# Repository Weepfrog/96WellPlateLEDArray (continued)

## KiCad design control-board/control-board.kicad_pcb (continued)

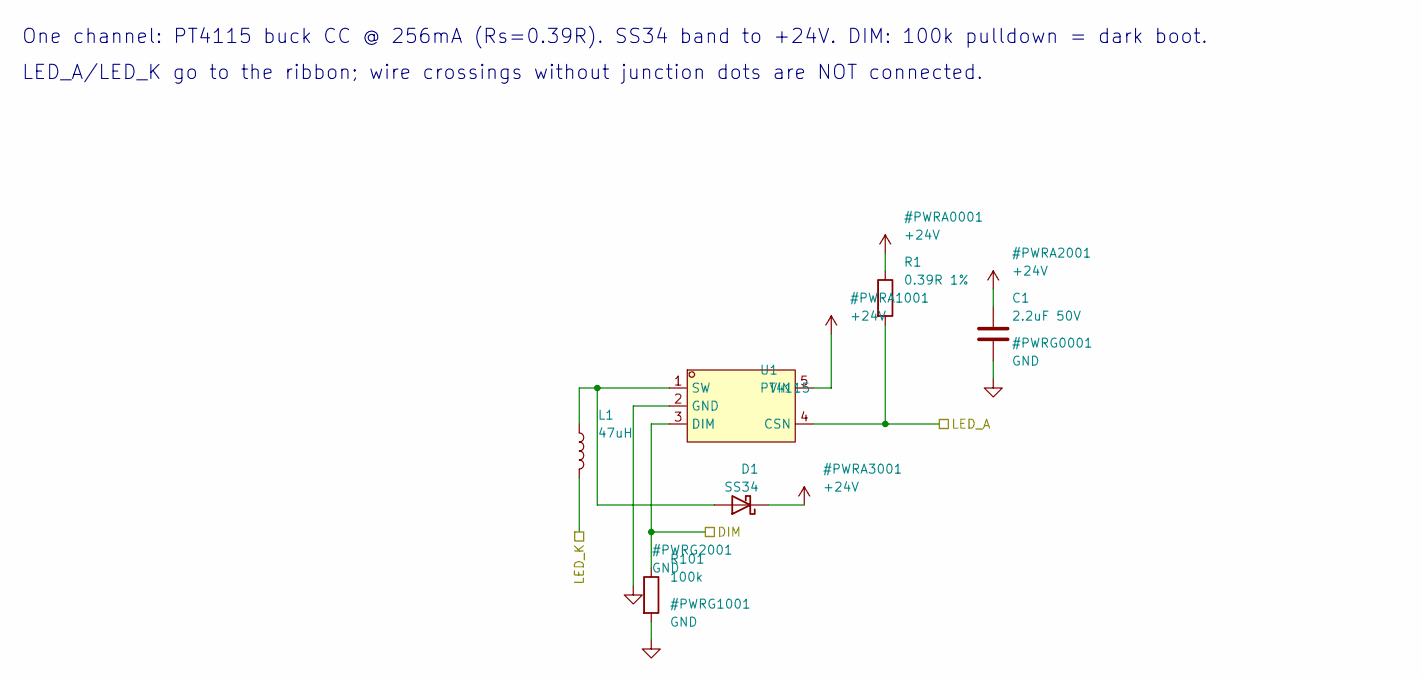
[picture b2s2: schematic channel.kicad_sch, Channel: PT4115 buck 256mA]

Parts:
C1: 2.2uF 50V; C_0805_2012Metric; LCSC C125847
D1: SS34; D_SMA; LCSC C8678
L1: 47uH; L_Sunlord_SWPA4030S; LCSC C54731
R1: 0.39R 1%; R_0805_2012Metric; LCSC C2930218
R101: 100k; R_0603_1608Metric; LCSC C25803
U1: PT4115; SOT-89-5_L4.5-W2.5-P1.50-LS4.5-BR; LCSC C347356

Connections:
+24V: C1.1, D1.1 (K), R1.1, U1.5 (VIN); also elsewhere on the board
/DIM1: R101.1, U1.3 (DIM); also elsewhere on the board
/LED_A33: R1.2, U1.4 (CSN); also elsewhere on the board
/LED_K33: L1.2; also elsewhere on the board
GND: C1.2, R101.2, U1.2 (GND); also elsewhere on the board
unnamed: D1.2 (A), L1.1, U1.1 (SW)

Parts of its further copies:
C2, C3, C4, C5, C6, C7, C8, C9, C10, C11, C12, C13, C14, C15, C16, C17, C18, C19, C20, C21, C22, C23, C24, C25, C26, C27, C28, C29, C30, C31, C32, C33, C34, C35, C36, C37, C38, C39, C40, C41, C42, C43, C44, C45, C46, C47, C48, C49, C50, C51, C52, C53, C54, C55, C56, C57, C58, C59, C60, C61, C62, C63, C64, C65, C66, C67, C68, C69, C70, C71, C72, C73, C74, C75, C76, C77, C78, C79, C80, C81, C82, C83, C84, C85, C86, C87, C88, C89, C90, C91, C92, C93, C94, C95, C96: 2.2uF 50V; C_0805_2012Metric; LCSC C125847
D2, D3, D4, D5, D6, D7, D8, D9, D10, D11, D12, D13, D14, D15, D16, D17, D18, D19, D20, D21, D22, D23, D24, D25, D26, D27, D28, D29, D30, D31, D32, D33, D34, D35, D36, D37, D38, D39, D40, D41, D42, D43, D44, D45, D46, D47, D48, D49, D50, D51, D52, D53, D54, D55, D56, D57, D58, D59, D60, D61, D62, D63, D64, D65, D66, D67, D68, D69, D70, D71, D72, D73, D74, D75, D76, D77, D78, D79, D80, D81, D82, D83, D84, D85, D86, D87, D88, D89, D90, D91, D92, D93, D94, D95, D96: SS34; D_SMA; LCSC C8678
L2, L3, L4, L5, L6, L7, L8, L9, L10, L11, L12, L13, L14, L15, L16, L17, L18, L19, L20, L21, L22, L23, L24, L25, L26, L27, L28, L29, L30, L31, L32, L33, L34, L35, L36, L37, L38, L39, L40, L41, L42, L43, L44, L45, L46, L47, L48, L49, L50, L51, L52, L53, L54, L55, L56, L57, L58, L59, L60, L61, L62, L63, L64, L65, L66, L67, L68, L69, L70, L71, L72, L73, L74, L75, L76, L77, L78, L79, L80, L81, L82, L83, L84, L85, L86, L87, L88, L89, L90, L91, L92, L93, L94, L95, L96: 47uH; L_Sunlord_SWPA4030S; LCSC C54731
R2, R3, R4, R5, R6, R7, R8, R9, R10, R11, R12, R13, R14, R15, R16, R17, R18, R19, R20, R21, R22, R23, R24, R25, R26, R27, R28, R29, R30, R31, R32, R33, R34, R35, R36, R37, R38, R39, R40, R41, R42, R43, R44, R45, R46, R47, R48, R49, R50, R51, R52, R53, R54, R55, R56, R57, R58, R59, R60, R61, R62, R63, R64, R65, R66, R67, R68, R69, R70, R71, R72, R73, R74, R75, R76, R77, R78, R79, R80, R81, R82, R83, R84, R85, R86, R87, R88, R89, R90, R91, R92, R93, R94, R95, R96: 0.39R 1%; R_0805_2012Metric; LCSC C2930218
R102, R103, R104, R105, R106, R107, R108, R109, R110, R111, R112, R113, R114, R115, R116, R117, R118, R119, R120, R121, R122, R123, R124, R125, R126, R127, R128, R129, R130, R131, R132, R133, R134, R135, R136, R137, R138, R139, R140, R141, R142, R143, R144, R145, R146, R147, R148, R149, R150, R151, R152, R153, R154, R155, R156, R157, R158, R159, R160, R161, R162, R163, R164, R165, R166, R167, R168, R169, R170, R171, R172, R173, R174, R175, R176, R177, R178, R179, R180, R181, R182, R183, R184, R185, R186, R187, R188, R189, R190, R191, R192, R193, R194, R195, R196: 100k; R_0603_1608Metric; LCSC C25803
U2, U3, U4, U5, U6, U7, U8, U9, U10, U11, U12, U13, U14, U15, U16, U17, U18, U19, U20, U21, U22, U23, U24, U25, U26, U27, U28, U29, U30, U31, U32, U33, U34, U35, U36, U37, U38, U39, U40, U41, U42, U43, U44, U45, U46, U47, U48, U49, U50, U51, U52, U53, U54, U55, U56, U57, U58, U59, U60, U61, U62, U63, U64, U65, U66, U67, U68, U69, U70, U71, U72, U73, U74, U75, U76, U77, U78, U79, U80, U81, U82, U83, U84, U85, U86, U87, U88, U89, U90, U91, U92, U93, U94, U95, U96: PT4115; SOT-89-5_L4.5-W2.5-P1.50-LS4.5-BR; LCSC C347356

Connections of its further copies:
+24V: C2.1, C3.1, C4.1, C5.1, C6.1, C7.1, C8.1, C9.1, C10.1, C11.1, C12.1, C13.1, C14.1, C15.1, C16.1, C17.1, C18.1, C19.1, C20.1, C21.1, C22.1, C23.1, C24.1, C25.1, C26.1, C27.1, C28.1, C29.1, C30.1, C31.1, C32.1, C33.1, C34.1, C35.1, C36.1, C37.1, C38.1, C39.1, C40.1, C41.1, C42.1, C43.1, C44.1, C45.1, C46.1, C47.1, C48.1, C49.1, C50.1, C51.1, C52.1, C53.1, C54.1, C55.1, C56.1, C57.1, C58.1, C59.1, C60.1, C61.1, C62.1, C63.1, C64.1, C65.1, C66.1, C67.1, C68.1, C69.1, C70.1, C71.1, C72.1, C73.1, C74.1, C75.1, C76.1, C77.1, C78.1, C79.1, C80.1, C81.1, C82.1, C83.1, C84.1, C85.1, C86.1, C87.1, C88.1, C89.1, C90.1, C91.1, C92.1, C93.1, C94.1, C95.1, C96.1, D2.1 (K), D3.1 (K), D4.1 (K), D5.1 (K), D6.1 (K), D7.1 (K), D8.1 (K), D9.1 (K), D10.1 (K), D11.1 (K), D12.1 (K), D13.1 (K), D14.1 (K), D15.1 (K), D16.1 (K), D17.1 (K), D18.1 (K), D19.1 (K), D20.1 (K), D21.1 (K), D22.1 (K), D23.1 (K), D24.1 (K), D25.1 (K), D26.1 (K), D27.1 (K), D28.1 (K), D29.1 (K), D30.1 (K), D31.1 (K), D32.1 (K), D33.1 (K), D34.1 (K), D35.1 (K), D36.1 (K), D37.1 (K), D38.1 (K), D39.1 (K), D40.1 (K), D41.1 (K), D42.1 (K), D43.1 (K), D44.1 (K), D45.1 (K), D46.1 (K), D47.1 (K), D48.1 (K), D49.1 (K), D50.1 (K), D51.1 (K), D52.1 (K), D53.1 (K), D54.1 (K), D55.1 (K), D56.1 (K), D57.1 (K), D58.1 (K), D59.1 (K), D60.1 (K), D61.1 (K), D62.1 (K), D63.1 (K), D64.1 (K), D65.1 (K), D66.1 (K), D67.1 (K), D68.1 (K), D69.1 (K), D70.1 (K), D71.1 (K), D72.1 (K), D73.1 (K), D74.1 (K), D75.1 (K), D76.1 (K), D77.1 (K), D78.1 (K), D79.1 (K), D80.1 (K), D81.1 (K), D82.1 (K), D83.1 (K), D84.1 (K), D85.1 (K), D86.1 (K), D87.1 (K), D88.1 (K), D89.1 (K), D90.1 (K), D91.1 (K), D92.1 (K), D93.1 (K), D94.1 (K), D95.1 (K), D96.1 (K), R2.1, R3.1, R4.1, R5.1, R6.1, R7.1, R8.1, R9.1, R10.1, R11.1, R12.1, R13.1, R14.1, R15.1, R16.1, R17.1, R18.1, R19.1, R20.1, R21.1, R22.1, R23.1, R24.1, R25.1, R26.1, R27.1, R28.1, R29.1, R30.1, R31.1, R32.1, R33.1, R34.1, R35.1, R36.1, R37.1, R38.1, R39.1, R40.1, R41.1, R42.1, R43.1, R44.1, R45.1, R46.1, R47.1, R48.1, R49.1, R50.1, R51.1, R52.1, R53.1, R54.1, R55.1, R56.1, R57.1, R58.1, R59.1, R60.1, R61.1, R62.1, R63.1, R64.1, R65.1, R66.1, R67.1, R68.1, R69.1, R70.1, R71.1, R72.1, R73.1, R74.1, R75.1, R76.1, R77.1, R78.1, R79.1, R80.1, R81.1, R82.1, R83.1, R84.1, R85.1, R86.1, R87.1, R88.1, R89.1, R90.1, R91.1, R92.1, R93.1, R94.1, R95.1, R96.1, U2.5 (VIN), U3.5 (VIN), U4.5 (VIN), U5.5 (VIN), U6.5 (VIN), U7.5 (VIN), U8.5 (VIN), U9.5 (VIN), U10.5 (VIN), U11.5 (VIN), U12.5 (VIN), U13.5 (VIN), U14.5 (VIN), U15.5 (VIN), U16.5 (VIN), U17.5 (VIN), U18.5 (VIN), U19.5 (VIN), U20.5 (VIN), U21.5 (VIN), U22.5 (VIN), U23.5 (VIN), U24.5 (VIN), U25.5 (VIN), U26.5 (VIN), U27.5 (VIN), U28.5 (VIN), U29.5 (VIN), U30.5 (VIN), U31.5 (VIN), U32.5 (VIN), U33.5 (VIN), U34.5 (VIN), U35.5 (VIN), U36.5 (VIN), U37.5 (VIN), U38.5 (VIN), U39.5 (VIN), U40.5 (VIN), U41.5 (VIN), U42.5 (VIN), U43.5 (VIN), U44.5 (VIN), U45.5 (VIN), U46.5 (VIN), U47.5 (VIN), U48.5 (VIN), U49.5 (VIN), U50.5 (VIN), U51.5 (VIN), U52.5 (VIN), U53.5 (VIN), U54.5 (VIN), U55.5 (VIN), U56.5 (VIN), U57.5 (VIN), U58.5 (VIN), U59.5 (VIN), U60.5 (VIN), U61.5 (VIN), U62.5 (VIN), U63.5 (VIN), U64.5 (VIN), U65.5 (VIN), U66.5 (VIN), U67.5 (VIN), U68.5 (VIN), U69.5 (VIN), U70.5 (VIN), U71.5 (VIN), U72.5 (VIN), U73.5 (VIN), U74.5 (VIN), U75.5 (VIN), U76.5 (VIN), U77.5 (VIN), U78.5 (VIN), U79.5 (VIN), U80.5 (VIN), U81.5 (VIN), U82.5 (VIN), U83.5 (VIN), U84.5 (VIN), U85.5 (VIN), U86.5 (VIN), U87.5 (VIN), U88.5 (VIN), U89.5 (VIN), U90.5 (VIN), U91.5 (VIN), U92.5 (VIN), U93.5 (VIN), U94.5 (VIN), U95.5 (VIN), U96.5 (VIN); also elsewhere on the board
/DIM2: R102.1, U2.3 (DIM); also elsewhere on the board
/DIM3: R103.1, U3.3 (DIM); also elsewhere on the board
/DIM4: R104.1, U4.3 (DIM); also elsewhere on the board
/DIM5: R105.1, U5.3 (DIM); also elsewhere on the board
/DIM6: R106.1, U6.3 (DIM); also elsewhere on the board
/DIM7: R107.1, U7.3 (DIM); also elsewhere on the board
/DIM8: R108.1, U8.3 (DIM); also elsewhere on the board
/DIM9: R109.1, U9.3 (DIM); also elsewhere on the board
/DIM10: R110.1, U10.3 (DIM); also elsewhere on the board
/DIM11: R111.1, U11.3 (DIM); also elsewhere on the board
/DIM12: R112.1, U12.3 (DIM); also elsewhere on the board
/DIM13: R113.1, U13.3 (DIM); also elsewhere on the board
/DIM14: R114.1, U14.3 (DIM); also elsewhere on the board
/DIM15: R115.1, U15.3 (DIM); also elsewhere on the board
/DIM16: R116.1, U16.3 (DIM); also elsewhere on the board
/DIM17: R117.1, U17.3 (DIM); also elsewhere on the board
/DIM18: R118.1, U18.3 (DIM); also elsewhere on the board
/DIM19: R119.1, U19.3 (DIM); also elsewhere on the board
/DIM20: R120.1, U20.3 (DIM); also elsewhere on the board
/DIM21: R121.1, U21.3 (DIM); also elsewhere on the board
/DIM22: R122.1, U22.3 (DIM); also elsewhere on the board
/DIM23: R123.1, U23.3 (DIM); also elsewhere on the board
/DIM24: R124.1, U24.3 (DIM); also elsewhere on the board
/DIM25: R125.1, U25.3 (DIM); also elsewhere on the board
/DIM26: R126.1, U26.3 (DIM); also elsewhere on the board
/DIM27: R127.1, U27.3 (DIM); also elsewhere on the board
/DIM28: R128.1, U28.3 (DIM); also elsewhere on the board
/DIM29: R129.1, U29.3 (DIM); also elsewhere on the board
/DIM30: R130.1, U30.3 (DIM); also elsewhere on the board
/DIM31: R131.1, U31.3 (DIM); also elsewhere on the board
/DIM32: R132.1, U32.3 (DIM); also elsewhere on the board
/DIM33: R133.1, U33.3 (DIM); also elsewhere on the board
/DIM34: R134.1, U34.3 (DIM); also elsewhere on the board
/DIM35: R135.1, U35.3 (DIM); also elsewhere on the board
/DIM36: R136.1, U36.3 (DIM); also elsewhere on the board
/DIM37: R137.1, U37.3 (DIM); also elsewhere on the board
/DIM38: R138.1, U38.3 (DIM); also elsewhere on the board
/DIM39: R139.1, U39.3 (DIM); also elsewhere on the board
/DIM40: R140.1, U40.3 (DIM); also elsewhere on the board
/DIM41: R141.1, U41.3 (DIM); also elsewhere on the board
/DIM42: R142.1, U42.3 (DIM); also elsewhere on the board
/DIM43: R143.1, U43.3 (DIM); also elsewhere on the board
/DIM44: R144.1, U44.3 (DIM); also elsewhere on the board
/DIM45: R145.1, U45.3 (DIM); also elsewhere on the board
/DIM46: R146.1, U46.3 (DIM); also elsewhere on the board
/DIM47: R147.1, U47.3 (DIM); also elsewhere on the board
/DIM48: R148.1, U48.3 (DIM); also elsewhere on the board
/DIM49: R149.1, U49.3 (DIM); also elsewhere on the board
/DIM50: R150.1, U50.3 (DIM); also elsewhere on the board
/DIM51: R151.1, U51.3 (DIM); also elsewhere on the board
/DIM52: R152.1, U52.3 (DIM); also elsewhere on the board
/DIM53: R153.1, U53.3 (DIM); also elsewhere on the board
/DIM54: R154.1, U54.3 (DIM); also elsewhere on the board
/DIM55: R155.1, U55.3 (DIM); also elsewhere on the board
/DIM56: R156.1, U56.3 (DIM); also elsewhere on the board
/DIM57: R157.1, U57.3 (DIM); also elsewhere on the board
/DIM58: R158.1, U58.3 (DIM); also elsewhere on the board
/DIM59: R159.1, U59.3 (DIM); also elsewhere on the board
/DIM60: R160.1, U60.3 (DIM); also elsewhere on the board
/DIM61: R161.1, U61.3 (DIM); also elsewhere on the board
/DIM62: R162.1, U62.3 (DIM); also elsewhere on the board
/DIM63: R163.1, U63.3 (DIM); also elsewhere on the board
/DIM64: R164.1, U64.3 (DIM); also elsewhere on the board
/DIM65: R165.1, U65.3 (DIM); also elsewhere on the board
/DIM66: R166.1, U66.3 (DIM); also elsewhere on the board
/DIM67: R167.1, U67.3 (DIM); also elsewhere on the board
/DIM68: R168.1, U68.3 (DIM); also elsewhere on the board
/DIM69: R169.1, U69.3 (DIM); also elsewhere on the board
/DIM70: R170.1, U70.3 (DIM); also elsewhere on the board
/DIM71: R171.1, U71.3 (DIM); also elsewhere on the board
/DIM72: R172.1, U72.3 (DIM); also elsewhere on the board
/DIM73: R173.1, U73.3 (DIM); also elsewhere on the board
/DIM74: R174.1, U74.3 (DIM); also elsewhere on the board
/DIM75: R175.1, U75.3 (DIM); also elsewhere on the board
/DIM76: R176.1, U76.3 (DIM); also elsewhere on the board
/DIM77: R177.1, U77.3 (DIM); also elsewhere on the board
/DIM78: R178.1, U78.3 (DIM); also elsewhere on the board
/DIM79: R179.1, U79.3 (DIM); also elsewhere on the board
/DIM80: R180.1, U80.3 (DIM); also elsewhere on the board
/DIM81: R181.1, U81.3 (DIM); also elsewhere on the board
/DIM82: R182.1, U82.3 (DIM); also elsewhere on the board
/DIM83: R183.1, U83.3 (DIM); also elsewhere on the board
/DIM84: R184.1, U84.3 (DIM); also elsewhere on the board
/DIM85: R185.1, U85.3 (DIM); also elsewhere on the board
/DIM86: R186.1, U86.3 (DIM); also elsewhere on the board
/DIM87: R187.1, U87.3 (DIM); also elsewhere on the board
/DIM88: R188.1, U88.3 (DIM); also elsewhere on the board
/DIM89: R189.1, U89.3 (DIM); also elsewhere on the board
/DIM90: R190.1, U90.3 (DIM); also elsewhere on the board
/DIM91: R191.1, U91.3 (DIM); also elsewhere on the board
/DIM92: R192.1, U92.3 (DIM); also elsewhere on the board
/DIM93: R193.1, U93.3 (DIM); also elsewhere on the board
/DIM94: R194.1, U94.3 (DIM); also elsewhere on the board
/DIM95: R195.1, U95.3 (DIM); also elsewhere on the board
/DIM96: R196.1, U96.3 (DIM); also elsewhere on the board
/LED_A1: R10.2, U10.4 (CSN); also elsewhere on the board
/LED_A2: R11.2, U11.4 (CSN); also elsewhere on the board
/LED_A3: R12.2, U12.4 (CSN); also elsewhere on the board
/LED_A4: R21.2, U21.4 (CSN); also elsewhere on the board
/LED_A5: R22.2, U22.4 (CSN); also elsewhere on the board
/LED_A6: R23.2, U23.4 (CSN); also elsewhere on the board
/LED_A7: R24.2, U24.4 (CSN); also elsewhere on the board
/LED_A8: R33.2, U33.4 (CSN); also elsewhere on the board
/LED_A9: R34.2, U34.4 (CSN); also elsewhere on the board
/LED_A10: R35.2, U35.4 (CSN); also elsewhere on the board
/LED_A11: R36.2, U36.4 (CSN); also elsewhere on the board
/LED_A12: R44.2, U44.4 (CSN); also elsewhere on the board
/LED_A13: R45.2, U45.4 (CSN); also elsewhere on the board
/LED_A14: R46.2, U46.4 (CSN); also elsewhere on the board
/LED_A15: R47.2, U47.4 (CSN); also elsewhere on the board
/LED_A16: R48.2, U48.4 (CSN); also elsewhere on the board
/LED_A17: R5.2, U5.4 (CSN); also elsewhere on the board
/LED_A18: R6.2, U6.4 (CSN); also elsewhere on the board
/LED_A19: R17.2, U17.4 (CSN); also elsewhere on the board
/LED_A20: R7.2, U7.4 (CSN); also elsewhere on the board
/LED_A21: R18.2, U18.4 (CSN); also elsewhere on the board
/LED_A22: R29.2, U29.4 (CSN); also elsewhere on the board
/LED_A23: R41.2, U41.4 (CSN); also elsewhere on the board
/LED_A24: R30.2, U30.4 (CSN); also elsewhere on the board
/LED_A25: R19.2, U19.4 (CSN); also elsewhere on the board
/LED_A26: R8.2, U8.4 (CSN); also elsewhere on the board
/LED_A27: R42.2, U42.4 (CSN); also elsewhere on the board
/LED_A28: R9.2, U9.4 (CSN); also elsewhere on the board
/LED_A29: R31.2, U31.4 (CSN); also elsewhere on the board
/LED_A30: R20.2, U20.4 (CSN); also elsewhere on the board
/LED_A31: R43.2, U43.4 (CSN); also elsewhere on the board
/LED_A32: R32.2, U32.4 (CSN); also elsewhere on the board
/LED_A34: R13.2, U13.4 (CSN); also elsewhere on the board
/LED_A35: R2.2, U2.4 (CSN); also elsewhere on the board
/LED_A36: R25.2, U25.4 (CSN); also elsewhere on the board
/LED_A37: R14.2, U14.4 (CSN); also elsewhere on the board
/LED_A38: R37.2, U37.4 (CSN); also elsewhere on the board
/LED_A39: R26.2, U26.4 (CSN); also elsewhere on the board
/LED_A40: R38.2, U38.4 (CSN); also elsewhere on the board
/LED_A41: R3.2, U3.4 (CSN); also elsewhere on the board
/LED_A42: R15.2, U15.4 (CSN); also elsewhere on the board
/LED_A43: R27.2, U27.4 (CSN); also elsewhere on the board
/LED_A44: R4.2, U4.4 (CSN); also elsewhere on the board
/LED_A45: R16.2, U16.4 (CSN); also elsewhere on the board
/LED_A46: R39.2, U39.4 (CSN); also elsewhere on the board
/LED_A47: R28.2, U28.4 (CSN); also elsewhere on the board
/LED_A48: R40.2, U40.4 (CSN); also elsewhere on the board
/LED_A49: R57.2, U57.4 (CSN); also elsewhere on the board
/LED_A50: R59.2, U59.4 (CSN); also elsewhere on the board
/LED_A51: R60.2, U60.4 (CSN); also elsewhere on the board
/LED_A52: R58.2, U58.4 (CSN); also elsewhere on the board
/LED_A53: R56.2, U56.4 (CSN); also elsewhere on the board
/LED_A54: R70.2, U70.4 (CSN); also elsewhere on the board
/LED_A55: R72.2, U72.4 (CSN); also elsewhere on the board
/LED_A56: R71.2, U71.4 (CSN); also elsewhere on the board
/LED_A57: R69.2, U69.4 (CSN); also elsewhere on the board
/LED_A58: R81.2, U81.4 (CSN); also elsewhere on the board
/LED_A59: R84.2, U84.4 (CSN); also elsewhere on the board
/LED_A60: R83.2, U83.4 (CSN); also elsewhere on the board
/LED_A61: R82.2, U82.4 (CSN); also elsewhere on the board
/LED_A62: R94.2, U94.4 (CSN); also elsewhere on the board
/LED_A63: R95.2, U95.4 (CSN); also elsewhere on the board
/LED_A64: R96.2, U96.4 (CSN); also elsewhere on the board
/LED_A65: R89.2, U89.4 (CSN); also elsewhere on the board
/LED_A66: R90.2, U90.4 (CSN); also elsewhere on the board
/LED_A67: R77.2, U77.4 (CSN); also elsewhere on the board
/LED_A68: R91.2, U91.4 (CSN); also elsewhere on the board
/LED_A69: R78.2, U78.4 (CSN); also elsewhere on the board
/LED_A70: R65.2, U65.4 (CSN); also elsewhere on the board
/LED_A71: R53.2, U53.4 (CSN); also elsewhere on the board
/LED_A72: R66.2, U66.4 (CSN); also elsewhere on the board
/LED_A73: R92.2, U92.4 (CSN); also elsewhere on the board
/LED_A74: R79.2, U79.4 (CSN); also elsewhere on the board
/LED_A75: R54.2, U54.4 (CSN); also elsewhere on the board
/LED_A76: R80.2, U80.4 (CSN); also elsewhere on the board
/LED_A77: R93.2, U93.4 (CSN); also elsewhere on the board
/LED_A78: R67.2, U67.4 (CSN); also elsewhere on the board
/LED_A79: R55.2, U55.4 (CSN); also elsewhere on the board
/LED_A80: R68.2, U68.4 (CSN); also elsewhere on the board
/LED_A81: R85.2, U85.4 (CSN); also elsewhere on the board
/LED_A82: R73.2, U73.4 (CSN); also elsewhere on the board
/LED_A83: R86.2, U86.4 (CSN); also elsewhere on the board
/LED_A84: R61.2, U61.4 (CSN); also elsewhere on the board
/LED_A85: R74.2, U74.4 (CSN); also elsewhere on the board
/LED_A86: R49.2, U49.4 (CSN); also elsewhere on the board
/LED_A87: R62.2, U62.4 (CSN); also elsewhere on the board
/LED_A88: R87.2, U87.4 (CSN); also elsewhere on the board
/LED_A89: R50.2, U50.4 (CSN); also elsewhere on the board
/LED_A90: R75.2, U75.4 (CSN); also elsewhere on the board
/LED_A91: R88.2, U88.4 (CSN); also elsewhere on the board
/LED_A92: R63.2, U63.4 (CSN); also elsewhere on the board
/LED_A93: R51.2, U51.4 (CSN); also elsewhere on the board
/LED_A94: R76.2, U76.4 (CSN); also elsewhere on the board
/LED_A95: R64.2, U64.4 (CSN); also elsewhere on the board
/LED_A96: R52.2, U52.4 (CSN); also elsewhere on the board
/LED_K1: L10.2; also elsewhere on the board
/LED_K2: L11.2; also elsewhere on the board
/LED_K3: L12.2; also elsewhere on the board
/LED_K4: L21.2; also elsewhere on the board
/LED_K5: L22.2; also elsewhere on the board
/LED_K6: L23.2; also elsewhere on the board
/LED_K7: L24.2; also elsewhere on the board
/LED_K8: L33.2; also elsewhere on the board
/LED_K9: L34.2; also elsewhere on the board
/LED_K10: L35.2; also elsewhere on the board
/LED_K11: L36.2; also elsewhere on the board
/LED_K12: L44.2; also elsewhere on the board
/LED_K13: L45.2; also elsewhere on the board
/LED_K14: L46.2; also elsewhere on the board
/LED_K15: L47.2; also elsewhere on the board
/LED_K16: L48.2; also elsewhere on the board
/LED_K17: L5.2; also elsewhere on the board
/LED_K18: L6.2; also elsewhere on the board
/LED_K19: L17.2; also elsewhere on the board
/LED_K20: L7.2; also elsewhere on the board
/LED_K21: L18.2; also elsewhere on the board
/LED_K22: L29.2; also elsewhere on the board
/LED_K23: L41.2; also elsewhere on the board
/LED_K24: L30.2; also elsewhere on the board
/LED_K25: L19.2; also elsewhere on the board
/LED_K26: L8.2; also elsewhere on the board
/LED_K27: L42.2; also elsewhere on the board
/LED_K28: L9.2; also elsewhere on the board
/LED_K29: L31.2; also elsewhere on the board
/LED_K30: L20.2; also elsewhere on the board
/LED_K31: L43.2; also elsewhere on the board
/LED_K32: L32.2; also elsewhere on the board
/LED_K34: L13.2; also elsewhere on the board
/LED_K35: L2.2; also elsewhere on the board
/LED_K36: L25.2; also elsewhere on the board
/LED_K37: L14.2; also elsewhere on the board
/LED_K38: L37.2; also elsewhere on the board
/LED_K39: L26.2; also elsewhere on the board
/LED_K40: L38.2; also elsewhere on the board
/LED_K41: L3.2; also elsewhere on the board
/LED_K42: L15.2; also elsewhere on the board
/LED_K43: L27.2; also elsewhere on the board
/LED_K44: L4.2; also elsewhere on the board
/LED_K45: L16.2; also elsewhere on the board
/LED_K46: L39.2; also elsewhere on the board
/LED_K47: L28.2; also elsewhere on the board
/LED_K48: L40.2; also elsewhere on the board
/LED_K49: L57.2; also elsewhere on the board
/LED_K50: L59.2; also elsewhere on the board
/LED_K51: L60.2; also elsewhere on the board
/LED_K52: L58.2; also elsewhere on the board
/LED_K53: L56.2; also elsewhere on the board
/LED_K54: L70.2; also elsewhere on the board
/LED_K55: L72.2; also elsewhere on the board
/LED_K56: L71.2; also elsewhere on the board
/LED_K57: L69.2; also elsewhere on the board
/LED_K58: L81.2; also elsewhere on the board
/LED_K59: L84.2; also elsewhere on the board
/LED_K60: L83.2; also elsewhere on the board
/LED_K61: L82.2; also elsewhere on the board
/LED_K62: L94.2; also elsewhere on the board
/LED_K63: L95.2; also elsewhere on the board
/LED_K64: L96.2; also elsewhere on the board
/LED_K65: L89.2; also elsewhere on the board
/LED_K66: L90.2; also elsewhere on the board
/LED_K67: L77.2; also elsewhere on the board
/LED_K68: L91.2; also elsewhere on the board
/LED_K69: L78.2; also elsewhere on the board
/LED_K70: L65.2; also elsewhere on the board
/LED_K71: L53.2; also elsewhere on the board
/LED_K72: L66.2; also elsewhere on the board
/LED_K73: L92.2; also elsewhere on the board
/LED_K74: L79.2; also elsewhere on the board
/LED_K75: L54.2; also elsewhere on the board
/LED_K76: L80.2; also elsewhere on the board
/LED_K77: L93.2; also elsewhere on the board
/LED_K78: L67.2; also elsewhere on the board
/LED_K79: L55.2; also elsewhere on the board
/LED_K80: L68.2; also elsewhere on the board
/LED_K81: L85.2; also elsewhere on the board
/LED_K82: L73.2; also elsewhere on the board
/LED_K83: L86.2; also elsewhere on the board
/LED_K84: L61.2; also elsewhere on the board
/LED_K85: L74.2; also elsewhere on the board
/LED_K86: L49.2; also elsewhere on the board
/LED_K87: L62.2; also elsewhere on the board
/LED_K88: L87.2; also elsewhere on the board
/LED_K89: L50.2; also elsewhere on the board
/LED_K90: L75.2; also elsewhere on the board
/LED_K91: L88.2; also elsewhere on the board
/LED_K92: L63.2; also elsewhere on the board
/LED_K93: L51.2; also elsewhere on the board
/LED_K94: L76.2; also elsewhere on the board
/LED_K95: L64.2; also elsewhere on the board
/LED_K96: L52.2; also elsewhere on the board
GND: C2.2, C3.2, C4.2, C5.2, C6.2, C7.2, C8.2, C9.2, C10.2, C11.2, C12.2, C13.2, C14.2, C15.2, C16.2, C17.2, C18.2, C19.2, C20.2, C21.2, C22.2, C23.2, C24.2, C25.2, C26.2, C27.2, C28.2, C29.2, C30.2, C31.2, C32.2, C33.2, C34.2, C35.2, C36.2, C37.2, C38.2, C39.2, C40.2, C41.2, C42.2, C43.2, C44.2, C45.2, C46.2, C47.2, C48.2, C49.2, C50.2, C51.2, C52.2, C53.2, C54.2, C55.2, C56.2, C57.2, C58.2, C59.2, C60.2, C61.2, C62.2, C63.2, C64.2, C65.2, C66.2, C67.2, C68.2, C69.2, C70.2, C71.2, C72.2, C73.2, C74.2, C75.2, C76.2, C77.2, C78.2, C79.2, C80.2, C81.2, C82.2, C83.2, C84.2, C85.2, C86.2, C87.2, C88.2, C89.2, C90.2, C91.2, C92.2, C93.2, C94.2, C95.2, C96.2, R102.2, R103.2, R104.2, R105.2, R106.2, R107.2, R108.2, R109.2, R110.2, R111.2, R112.2, R113.2, R114.2, R115.2, R116.2, R117.2, R118.2, R119.2, R120.2, R121.2, R122.2, R123.2, R124.2, R125.2, R126.2, R127.2, R128.2, R129.2, R130.2, R131.2, R132.2, R133.2, R134.2, R135.2, R136.2, R137.2, R138.2, R139.2, R140.2, R141.2, R142.2, R143.2, R144.2, R145.2, R146.2, R147.2, R148.2, R149.2, R150.2, R151.2, R152.2, R153.2, R154.2, R155.2, R156.2, R157.2, R158.2, R159.2, R160.2, R161.2, R162.2, R163.2, R164.2, R165.2, R166.2, R167.2, R168.2, R169.2, R170.2, R171.2, R172.2, R173.2, R174.2, R175.2, R176.2, R177.2, R178.2, R179.2, R180.2, R181.2, R182.2, R183.2, R184.2, R185.2, R186.2, R187.2, R188.2, R189.2, R190.2, R191.2, R192.2, R193.2, R194.2, R195.2, R196.2, U2.2 (GND), U3.2 (GND), U4.2 (GND), U5.2 (GND), U6.2 (GND), U7.2 (GND), U8.2 (GND), U9.2 (GND), U10.2 (GND), U11.2 (GND), U12.2 (GND), U13.2 (GND), U14.2 (GND), U15.2 (GND), U16.2 (GND), U17.2 (GND), U18.2 (GND), U19.2 (GND), U20.2 (GND), U21.2 (GND), U22.2 (GND), U23.2 (GND), U24.2 (GND), U25.2 (GND), U26.2 (GND), U27.2 (GND), U28.2 (GND), U29.2 (GND), U30.2 (GND), U31.2 (GND), U32.2 (GND), U33.2 (GND), U34.2 (GND), U35.2 (GND), U36.2 (GND), U37.2 (GND), U38.2 (GND), U39.2 (GND), U40.2 (GND), U41.2 (GND), U42.2 (GND), U43.2 (GND), U44.2 (GND), U45.2 (GND), U46.2 (GND), U47.2 (GND), U48.2 (GND), U49.2 (GND), U50.2 (GND), U51.2 (GND), U52.2 (GND), U53.2 (GND), U54.2 (GND), U55.2 (GND), U56.2 (GND), U57.2 (GND), U58.2 (GND), U59.2 (GND), U60.2 (GND), U61.2 (GND), U62.2 (GND), U63.2 (GND), U64.2 (GND), U65.2 (GND), U66.2 (GND), U67.2 (GND), U68.2 (GND), U69.2 (GND), U70.2 (GND), U71.2 (GND), U72.2 (GND), U73.2 (GND), U74.2 (GND), U75.2 (GND), U76.2 (GND), U77.2 (GND), U78.2 (GND), U79.2 (GND), U80.2 (GND), U81.2 (GND), U82.2 (GND), U83.2 (GND), U84.2 (GND), U85.2 (GND), U86.2 (GND), U87.2 (GND), U88.2 (GND), U89.2 (GND), U90.2 (GND), U91.2 (GND), U92.2 (GND), U93.2 (GND), U94.2 (GND), U95.2 (GND), U96.2 (GND); also elsewhere on the board
unnamed: D2.2 (A), L2.1, U2.1 (SW)
unnamed: D3.2 (A), L3.1, U3.1 (SW)
unnamed: D4.2 (A), L4.1, U4.1 (SW)
unnamed: D5.2 (A), L5.1, U5.1 (SW)
unnamed: D6.2 (A), L6.1, U6.1 (SW)
unnamed: D7.2 (A), L7.1, U7.1 (SW)
unnamed: D8.2 (A), L8.1, U8.1 (SW)
unnamed: D9.2 (A), L9.1, U9.1 (SW)
unnamed: D10.2 (A), L10.1, U10.1 (SW)
unnamed: D11.2 (A), L11.1, U11.1 (SW)
unnamed: D12.2 (A), L12.1, U12.1 (SW)
unnamed: D13.2 (A), L13.1, U13.1 (SW)
unnamed: D14.2 (A), L14.1, U14.1 (SW)
unnamed: D15.2 (A), L15.1, U15.1 (SW)
unnamed: D16.2 (A), L16.1, U16.1 (SW)
unnamed: D17.2 (A), L17.1, U17.1 (SW)
unnamed: D18.2 (A), L18.1, U18.1 (SW)
unnamed: D19.2 (A), L19.1, U19.1 (SW)
unnamed: D20.2 (A), L20.1, U20.1 (SW)
unnamed: D21.2 (A), L21.1, U21.1 (SW)
unnamed: D22.2 (A), L22.1, U22.1 (SW)
unnamed: D23.2 (A), L23.1, U23.1 (SW)
unnamed: D24.2 (A), L24.1, U24.1 (SW)
unnamed: D25.2 (A), L25.1, U25.1 (SW)
unnamed: D26.2 (A), L26.1, U26.1 (SW)
unnamed: D27.2 (A), L27.1, U27.1 (SW)
unnamed: D28.2 (A), L28.1, U28.1 (SW)
unnamed: D29.2 (A), L29.1, U29.1 (SW)
unnamed: D30.2 (A), L30.1, U30.1 (SW)
unnamed: D31.2 (A), L31.1, U31.1 (SW)
unnamed: D32.2 (A), L32.1, U32.1 (SW)
unnamed: D33.2 (A), L33.1, U33.1 (SW)
unnamed: D34.2 (A), L34.1, U34.1 (SW)
unnamed: D35.2 (A), L35.1, U35.1 (SW)
unnamed: D36.2 (A), L36.1, U36.1 (SW)
unnamed: D37.2 (A), L37.1, U37.1 (SW)
unnamed: D38.2 (A), L38.1, U38.1 (SW)
unnamed: D39.2 (A), L39.1, U39.1 (SW)
unnamed: D40.2 (A), L40.1, U40.1 (SW)
unnamed: D41.2 (A), L41.1, U41.1 (SW)
unnamed: D42.2 (A), L42.1, U42.1 (SW)
unnamed: D43.2 (A), L43.1, U43.1 (SW)
unnamed: D44.2 (A), L44.1, U44.1 (SW)
unnamed: D45.2 (A), L45.1, U45.1 (SW)
unnamed: D46.2 (A), L46.1, U46.1 (SW)
unnamed: D47.2 (A), L47.1, U47.1 (SW)
unnamed: D48.2 (A), L48.1, U48.1 (SW)
unnamed: D49.2 (A), L49.1, U49.1 (SW)
unnamed: D50.2 (A), L50.1, U50.1 (SW)
unnamed: D51.2 (A), L51.1, U51.1 (SW)
unnamed: D52.2 (A), L52.1, U52.1 (SW)
unnamed: D53.2 (A), L53.1, U53.1 (SW)
unnamed: D54.2 (A), L54.1, U54.1 (SW)
unnamed: D55.2 (A), L55.1, U55.1 (SW)
unnamed: D56.2 (A), L56.1, U56.1 (SW)
unnamed: D57.2 (A), L57.1, U57.1 (SW)
unnamed: D58.2 (A), L58.1, U58.1 (SW)
unnamed: D59.2 (A), L59.1, U59.1 (SW)
unnamed: D60.2 (A), L60.1, U60.1 (SW)
unnamed: D61.2 (A), L61.1, U61.1 (SW)
unnamed: D62.2 (A), L62.1, U62.1 (SW)
unnamed: D63.2 (A), L63.1, U63.1 (SW)
unnamed: D64.2 (A), L64.1, U64.1 (SW)
unnamed: D65.2 (A), L65.1, U65.1 (SW)
unnamed: D66.2 (A), L66.1, U66.1 (SW)
unnamed: D67.2 (A), L67.1, U67.1 (SW)
unnamed: D68.2 (A), L68.1, U68.1 (SW)
unnamed: D69.2 (A), L69.1, U69.1 (SW)
unnamed: D70.2 (A), L70.1, U70.1 (SW)
unnamed: D71.2 (A), L71.1, U71.1 (SW)
unnamed: D72.2 (A), L72.1, U72.1 (SW)
unnamed: D73.2 (A), L73.1, U73.1 (SW)
unnamed: D74.2 (A), L74.1, U74.1 (SW)
unnamed: D75.2 (A), L75.1, U75.1 (SW)
unnamed: D76.2 (A), L76.1, U76.1 (SW)
unnamed: D77.2 (A), L77.1, U77.1 (SW)
unnamed: D78.2 (A), L78.1, U78.1 (SW)
unnamed: D79.2 (A), L79.1, U79.1 (SW)
unnamed: D80.2 (A), L80.1, U80.1 (SW)
unnamed: D81.2 (A), L81.1, U81.1 (SW)
unnamed: D82.2 (A), L82.1, U82.1 (SW)
unnamed: D83.2 (A), L83.1, U83.1 (SW)
unnamed: D84.2 (A), L84.1, U84.1 (SW)
unnamed: D85.2 (A), L85.1, U85.1 (SW)
unnamed: D86.2 (A), L86.1, U86.1 (SW)
unnamed: D87.2 (A), L87.1, U87.1 (SW)
unnamed: D88.2 (A), L88.1, U88.1 (SW)
unnamed: D89.2 (A), L89.1, U89.1 (SW)
unnamed: D90.2 (A), L90.1, U90.1 (SW)
unnamed: D91.2 (A), L91.1, U91.1 (SW)
unnamed: D92.2 (A), L92.1, U92.1 (SW)
unnamed: D93.2 (A), L93.1, U93.1 (SW)
unnamed: D94.2 (A), L94.1, U94.1 (SW)
unnamed: D95.2 (A), L95.1, U95.1 (SW)
unnamed: D96.2 (A), L96.1, U96.1 (SW)

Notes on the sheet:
One channel: PT4115 buck CC @ 256mA (Rs=0.39R). SS34 band to +24V. DIM: 100k pulldown = dark boot.
LED_A/LED_K go to the ribbon; wire crossings without junction dots are NOT connected.

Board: 4 copper layers, 641 parts (0 on the bottom side), 412 nets, no tracks yet.

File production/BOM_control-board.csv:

Comment,Designator,Footprint,LCSC
2.2uF 50V,"C1,C10,C11,C12,C13,C14,C15,C16,C17,C18,C19,C2,C20,C21,C22,C23,C24,C25,C26,C27,C28,C29,C3,C30,C31,C32,C33,C34,C35,C36,C37,C38,C39,C4,C40,C41,C42,C43,C44,C45,C46,C47,C48,C49,C5,C50,C51,C52,C53,C54,C55,C56,C57,C58,C59,C6,C60,C61,C62,C63,C64,C65,C66,C67,C68,C69,C7,C70,C71,C72,C73,C74,C75,C76,C77,C78,C79,C8,C80,C81,C82,C83,C84,C85,C86,C87,C88,C89,C9,C90,C91,C92,C93,C94,C95,C96",C_0805_2012Metric,C125847
100uF 50V,C110,CP_Elec_8x10,C134514
220uF 35V,"C101,C102,C103,C104",CP_Elec_8x10,C134820
100nF,"C121,C122,C123,C124,C125,C126",C_0603_1608Metric,C14663
AO3400A,Q1,SOT-23,C20917
1k,"R204,R205",R_0603_1608Metric,C21190
100R,R201,R_0603_1608Metric,C22775
STATUS blue,LED2,LED_0805_2012Metric,C2293
PWR green,LED1,LED_0805_2012Metric,C2297
4.7k,"R210,R211",R_0603_1608Metric,C23162
100k,"R101,R102,R103,R104,R105,R106,R107,R108,R109,R110,R111,R112,R113,R114,R115,R116,R117,R118,R119,R120,R121,R122,R123,R124,R125,R126,R127,R128,R129,R130,R131,R132,R133,R134,R135,R136,R137,R138,R139,R140,R141,R142,R143,R144,R145,R146,R147,R148,R149,R150,R151,R152,R153,R154,R155,R156,R157,R158,R159,R160,R161,R162,R163,R164,R165,R166,R167,R168,R169,R170,R171,R172,R173,R174,R175,R176,R177,R178,R179,R180,R181,R182,R183,R184,R185,R186,R187,R188,R189,R190,R191,R192,R193,R194,R195,R196,R202",R_0603_1608Metric,C25803
PCA9685PW (0x40),U101,TSSOP-28_4.4x9.7mm_P0.65mm,C2678753
PCA9685PW (0x41),U102,TSSOP-28_4.4x9.7mm_P0.65mm,C2678753
PCA9685PW (0x42),U103,TSSOP-28_4.4x9.7mm_P0.65mm,C2678753
PCA9685PW (0x43),U104,TSSOP-28_4.4x9.7mm_P0.65mm,C2678753
PCA9685PW (0x44),U105,TSSOP-28_4.4x9.7mm_P0.65mm,C2678753
PCA9685PW (0x45),U106,TSSOP-28_4.4x9.7mm_P0.65mm,C2678753
220uF 16V,C111,CP_Elec_6.3x7.7,C286136
0.39R 1%,"R1,R10,R11,R12,R13,R14,R15,R16,R17,R18,R19,R2,R20,R21,R22,R23,R24,R25,R26,R27,R28,R29,R3,R30,R31,R32,R33,R34,R35,R36,R37,R38,R39,R4,R40,R41,R42,R43,R44,R45,R46,R47,R48,R49,R5,R50,R51,R52,R53,R54,R55,R56,R57,R58,R59,R6,R60,R61,R62,R63,R64,R65,R66,R67,R68,R69,R7,R70,R71,R72,R73,R74,R75,R76,R77,R78,R79,R8,R80,R81,R82,R83,R84,R85,R86,R87,R88,R89,R9,R90,R91,R92,R93,R94,R95,R96",R_0805_2012Metric,C2930218
MODE,SW1,SW-SMD_4P-L5.1-W5.1-P3.70-LS6.5-TL_H1.5,C318884
UP,SW2,SW-SMD_4P-L5.1-W5.1-P3.70-LS6.5-TL_H1.5,C318884
DOWN,SW3,SW-SMD_4P-L5.1-W5.1-P3.70-LS6.5-TL_H1.5,C318884
PT4115,"U1,U10,U11,U12,U13,U14,U15,U16,U17,U18,U19,U2,U20,U21,U22,U23,U24,U25,U26,U27,U28,U29,U3,U30,U31,U32,U33,U34,U35,U36,U37,U38,U39,U4,U40,U41,U42,U43,U44,U45,U46,U47,U48,U49,U5,U50,U51,U52,U53,U54,U55,U56,U57,U58,U59,U6,U60,U61,U62,U63,U64,U65,U66,U67,U68,U69,U7,U70,U71,U72,U73,U74,U75,U76,U77,U78,U79,U8,U80,U81,U82,U83,U84,U85,U86,U87,U88,U89,U9,U90,U91,U92,U93,U94,U95,U96",SOT-89-5_L4.5-W2.5-P1.50-LS4.5-BR,C347356
47uH 2A+,L101,L_Sunlord_SWPA6045S,C36414
2.2k,R203,R_0603_1608Metric,C4190
47uH,"L1,L10,L11,L12,L13,L14,L15,L16,L17,L18,L19,L2,L20,L21,L22,L23,L24,L25,L26,L27,L28,L29,L3,L30,L31,L32,L33,L34,L35,L36,L37,L38,L39,L4,L40,L41,L42,L43,L44,L45,L46,L47,L48,L49,L5,L50,L51,L52,L53,L54,L55,L56,L57,L58,L59,L6,L60,L61,L62,L63,L64,L65,L66,L67,L68,L69,L7,L70,L71,L72,L73,L74,L75,L76,L77,L78,L79,L8,L80,L81,L82,L83,L84,L85,L86,L87,L88,L89,L9,L90,L91,L92,L93,L94,L95,L96",L_Sunlord_SWPA4030S,C54731
XL1509-5.0E1,U110,SOIC-8_3.9x4.9mm_P1.27mm,C61063
FAULT red,LED3,LED_0805_2012Metric,C84256
SS34,"D1,D10,D101,D102,D11,D12,D13,D14,D15,D16,D17,D18,D19,D2,D20,D21,D22,D23,D24,D25,D26,D27,D28,D29,D3,D30,D31,D32,D33,D34,D35,D36,D37,D38,D39,D4,D40,D41,D42,D43,D44,D45,D46,D47,D48,D49,D5,D50,D51,D52,D53,D54,D55,D56,D57,D58,D59,D6,D60,D61,D62,D63,D64,D65,D66,D67,D68,D69,D7,D70,D71,D72,D73,D74,D75,D76,D77,D78,D79,D8,D80,D81,D82,D83,D84,D85,D86,D87,D88,D89,D9,D90,D91,D92,D93,D94,D95,D96",D_SMA,C8678

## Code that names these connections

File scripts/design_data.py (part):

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GPIO_PLAN = {
    "GPIO21": "I2C SDA (PCA9685 x6, ADS1115 opt.)",
    "GPIO22": "I2C SCL",
    "GPIO16": "MUX_A0", "GPIO17": "MUX_A1", "GPIO18": "MUX_A2",
    "GPIO19": "MUX_A3",
    "GPIO32": "NTC_SIG1 (ADC1_CH4)", "GPIO33": "NTC_SIG2 (ADC1_CH5)",
    "GPIO34": "NTC_SIG3 (ADC1_CH6)", "GPIO35": "NTC_SIG4 (ADC1_CH7)",
    "GPIO36/VP": "NTC_SIG5 (ADC1_CH0)", "GPIO39/VN": "NTC_SIG6 (ADC1_CH3)",
    "GPIO25": "FAN_PWM (Q1 gate via R201)",
    "GPIO4": "STATUS LED2 (blue)", "GPIO13": "FAULT LED3 (red)",
    "GPIO14": "SW1 MODE (to GND, internal pull-up)",
    "GPIO27": "SW2 UP (to GND, internal pull-up)",
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        net("GND", u, PCA_PINS["GND"])
        net("GND", u, PCA_PINS["OE"])           # outputs live at reset (LOW)
        net("GND", u, PCA_PINS["EXTCLK"])       # unused, tie low
        net("I2C_SDA", u, PCA_PINS["SDA"])
        net("I2C_SCL", u, PCA_PINS["SCL"])
        # address straps: 0x40+k -> A5..A0 = k in binary (A6 fixed 1 internally)
        for bit, pname in enumerate(["A0", "A1", "A2", "A3", "A4", "A5"]):
            net("+3.3V" if (k >> bit) & 1 else "GND", u, PCA_PINS[pname])
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    ]
    for i, name in enumerate(ESP32_J10, 1):
        sig = {"3V3": "+3.3V", "5V": "+5V", "GND": "GND",
               "GPIO36/VP": "NTC_SIG5", "GPIO39/VN": "NTC_SIG6",
               "GPIO34": "NTC_SIG3", "GPIO35": "NTC_SIG4",
               "GPIO32": "NTC_SIG1", "GPIO33": "NTC_SIG2",
               "GPIO25": "FAN_PWM", "GPIO26": "BTN_DOWN", "GPIO27": "BTN_UP",
               "GPIO14": "BTN_MODE", "GPIO13": "LED_FAULT",
               }.get(name)
        if sig:
            net(sig, "J10", i)
    for i, name in enumerate(ESP32_J11, 1):
        sig = {"GND": "GND", "GPIO22": "I2C_SCL", "GPIO21": "I2C_SDA",
               "GPIO19": "MUX_A3", "GPIO18": "MUX_A2", "GPIO17": "MUX_A1",
               "GPIO16": "MUX_A0", "GPIO4": "LED_STATUS",
               }.get(name)
        if sig:
            net(sig, "J11", i)
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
